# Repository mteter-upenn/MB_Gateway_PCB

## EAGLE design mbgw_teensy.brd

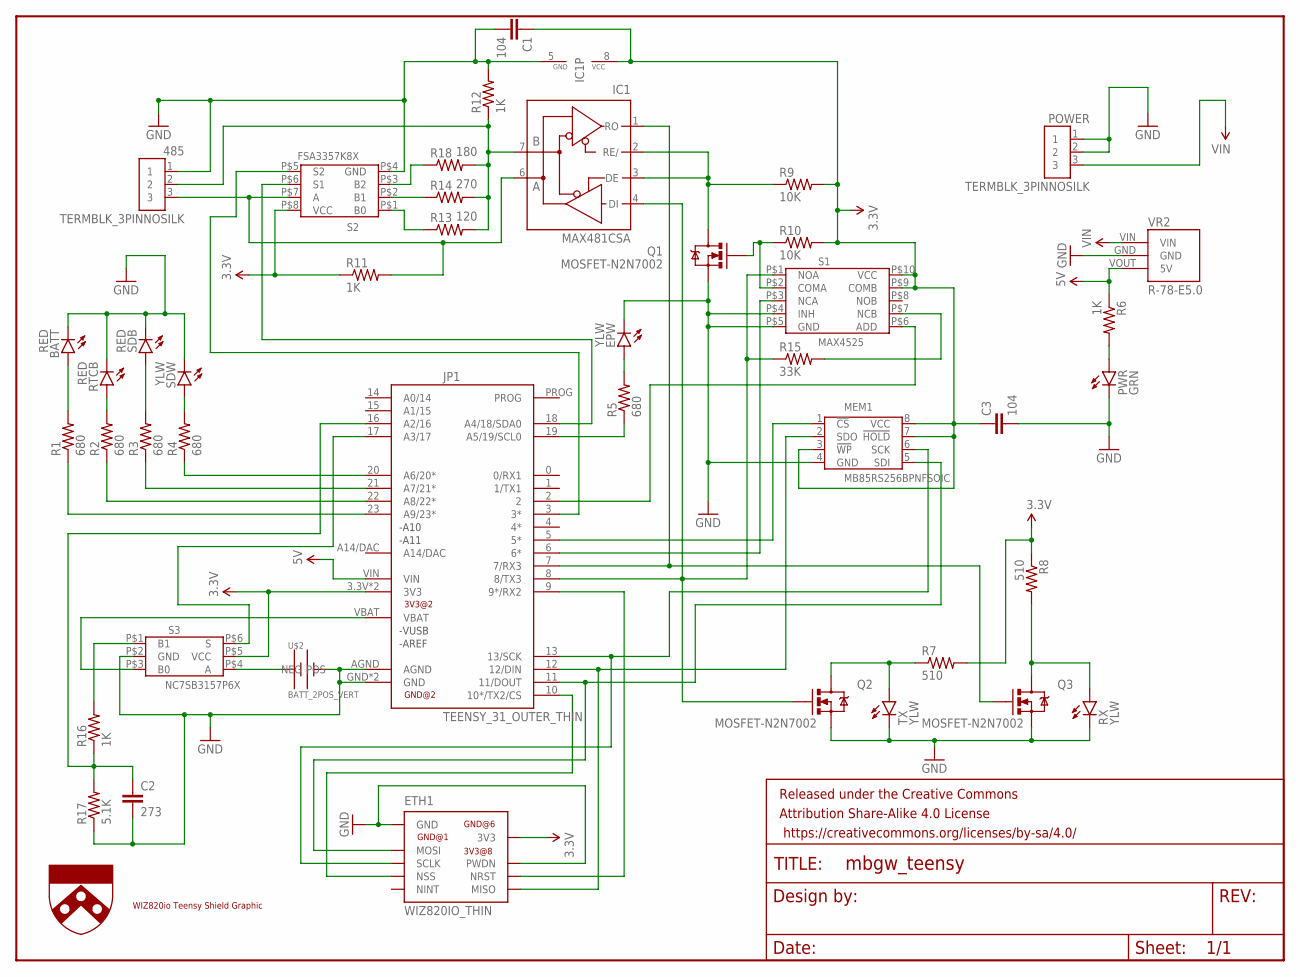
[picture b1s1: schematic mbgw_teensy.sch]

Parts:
485: TERMBLK_3PINNOSILK; TERMBLK_3PIN_90_NOSILK
BATT: RED; LED-0603
C1, C3: 104; 0603-CAP
C2: 273; 0603-CAP
EPW: YLW; LED-0603
ETH1: WIZ820IO_THIN
FRAME1: FRAME-LETTERNO_PACKAGE; DUMMY
IC1: MAX481CSA; SO08
JP1: TEENSY_31_OUTER_THIN; TEENSY-3.1_OUTER_THIN
MEM1: MB85RS256BPNFSOIC; SO08
POWER: TERMBLK_3PINNOSILK; TERMBLK_3PIN_90_NOSILK
PWR: GRN; LED-0603
Q1, Q2, Q3: MOSFET-N2N7002; SOT23-3
R1, R2, R3, R4, R5: 680; 0603-RES
R6, R11, R12, R16: 1K; 0603-RES
R7, R8: 510; 0603-RES
R9, R10: 10K; 0603-RES
R13: 120; 0603-RES
R14: 270; 0603-RES
R15: 33K; 0603-RES
R17: 5.1K; 0603-RES
R18: 180; 0603-RES
RTCB: RED; LED-0603
RX: YLW; LED-0603
S1: MAX4525; 3MM_10PIN
S2: FSA3357K8X; 2.3MM_8PIN
S3: NC7SB3157P6X; 1.25MM_6PIN
SDB: RED; LED-0603
SDW: YLW; LED-0603
TX: YLW; LED-0603
U$1: WIZ820_SHLD_OVRLY; WIZ820_SHLD_OVERLAY
U$2: BATT_2POS_VERT; BATTCONN_20MM_VERT
U$4: UPENN_SHIELD_.3_SILK; UPENN_SHIELD_3_SILK
VR2: R-78-E5.0; R-78-EXX

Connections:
3.3V: C1.1, C3.1, ETH1.3V3@7 (3V3), ETH1.3V3@8 (3V3), IC1.8 (VCC), JP1.3.3V (3V3), JP1.3V (3V3), MEM1.3 (!WP!), MEM1.7 (!HOLD!), MEM1.8 (VCC), R7.2, R8.1, R9.2, R10.2, R11.1, S1.P$9 (COMB), S1.P$10 (VCC), S2.P$8 (VCC), S3.P$5 (VCC)
5V: JP1.VIN, R6.1, VR2.VOUT (5V)
GND: 485.1, BATT.C, C1.2, C2.2, C3.2, EPW.C, ETH1.GND@0 (GND), ETH1.GND@1 (GND), ETH1.GND@6 (GND), ETH1.PWDN, IC1.5 (GND), JP1.AGND, JP1.GND, JP1.GND1 (GND), MEM1.4 (GND), POWER.1, POWER.2, PWR.C, Q1.2 (S), Q2.2 (S), Q3.2 (S), R12.2, R17.1, RTCB.C, RX.C, S1.P$4 (INH), S1.P$5 (GND), S2.P$4 (GND), S3.P$2 (GND), SDB.C, SDW.C, TX.C, U$2.NEG, VR2.GND
unnamed: R15.2, S1.P$7 (NCB)
unnamed: JP1.6 (6*), S1.P$3 (NCA)
unnamed: S3.P$4 (A), U$2.POS@1 (POS), U$2.POS@2 (POS)
unnamed: JP1.19 (A5/19/SCL0), R5.1
unnamed: ETH1.NSS, JP1.10 (10*/TX2/CS)
unnamed: ETH1.MOSI, JP1.11 (11/DOUT), MEM1.5 (SDI)
unnamed: ETH1.MISO, JP1.12 (12/DIN), MEM1.2 (SDO)
unnamed: ETH1.SCLK, JP1.13 (13/SCK), MEM1.6 (SCK)
unnamed: JP1.23 (A9/23*), R1.1
unnamed: ETH1.NRST, JP1.9 (9*/RX2)
unnamed: EPW.A, R5.2
unnamed: R13.1, S2.P$1 (B0)
unnamed: 485.2, IC1.7 (B), R12.1, R13.2, R14.2, R18.2
unnamed: PWR.A, R6.2
unnamed: JP1.18 (A4/18/SDA0), S2.P$6 (S1)
unnamed: IC1.1 (RO), JP1.7 (7/RX3), Q3.1 (G)
unnamed: IC1.4 (DI), JP1.8 (8/TX3), Q2.1 (G), R15.1, S1.P$1 (NOA)
unnamed: BATT.A, R1.2
unnamed: R3.2, SDB.A
unnamed: R2.2, RTCB.A
unnamed: R4.2, SDW.A
unnamed: JP1.22 (A8/22*), R2.1
unnamed: JP1.21 (A7/21*), R3.1
unnamed: JP1.20 (A6/20*), R4.1
unnamed: 485.3, IC1.6 (A), R11.2, S2.P$7 (A)
unnamed: Q1.1 (G), R10.1, S1.P$2 (COMA)
unnamed: IC1.2 (RE/), IC1.3 (DE), Q1.3 (D), R9.1
unnamed: Q3.3 (D), R8.2, RX.A
unnamed: Q2.3 (D), R7.1, TX.A
unnamed: R14.1, S2.P$2 (B1)
unnamed: JP1.3 (3*), S2.P$5 (S2)
unnamed: JP1.2, S1.P$6 (ADD)
unnamed: JP1.VBAT, S3.P$3 (B0)
unnamed: R18.1, S2.P$3 (B2)
unnamed: C2.1, JP1.16 (A2/16), R16.1, R17.2
unnamed: JP1.5 (5*), MEM1.1 (!CS!)
unnamed: R16.2, S3.P$1 (B1)
unnamed: JP1.17 (A3/17), S3.P$6 (S)
VIN: POWER.3, VR2.VIN

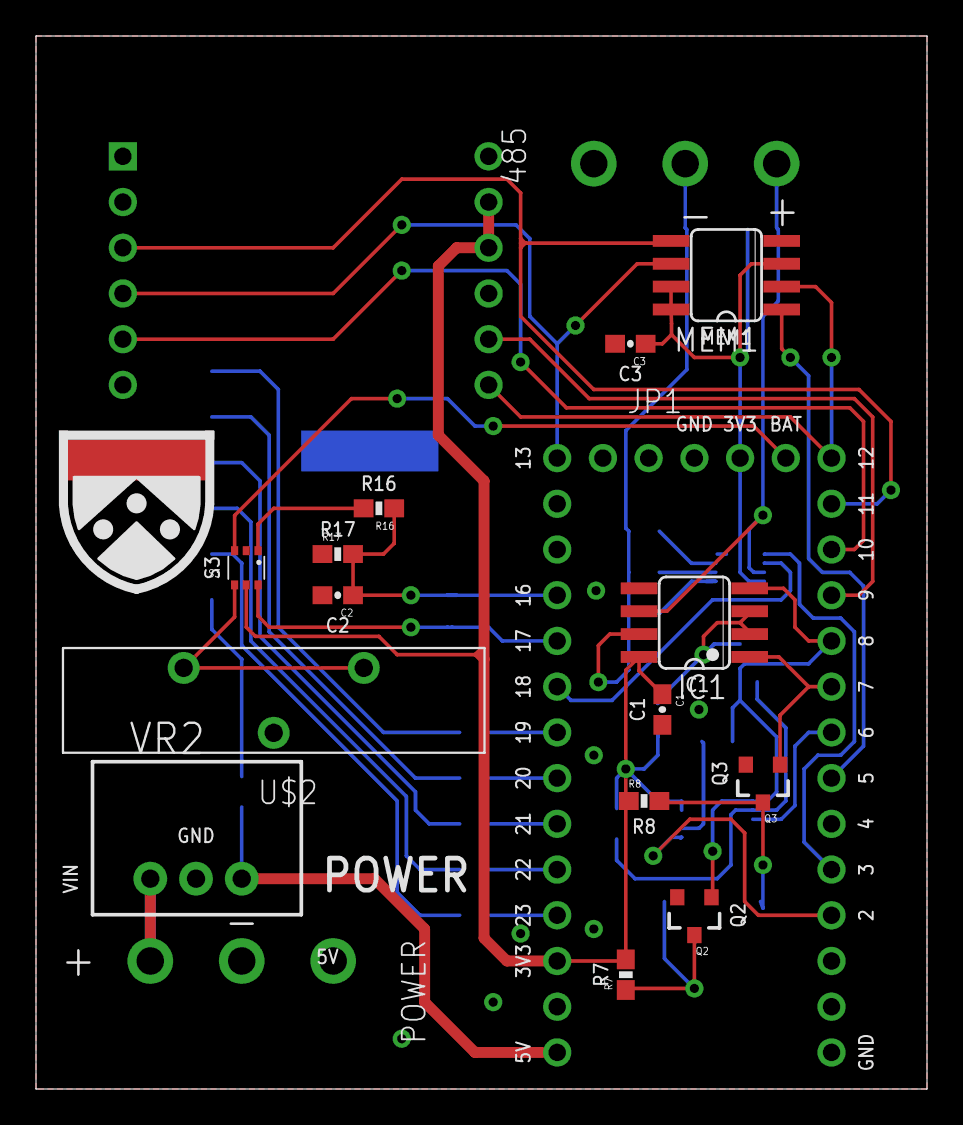
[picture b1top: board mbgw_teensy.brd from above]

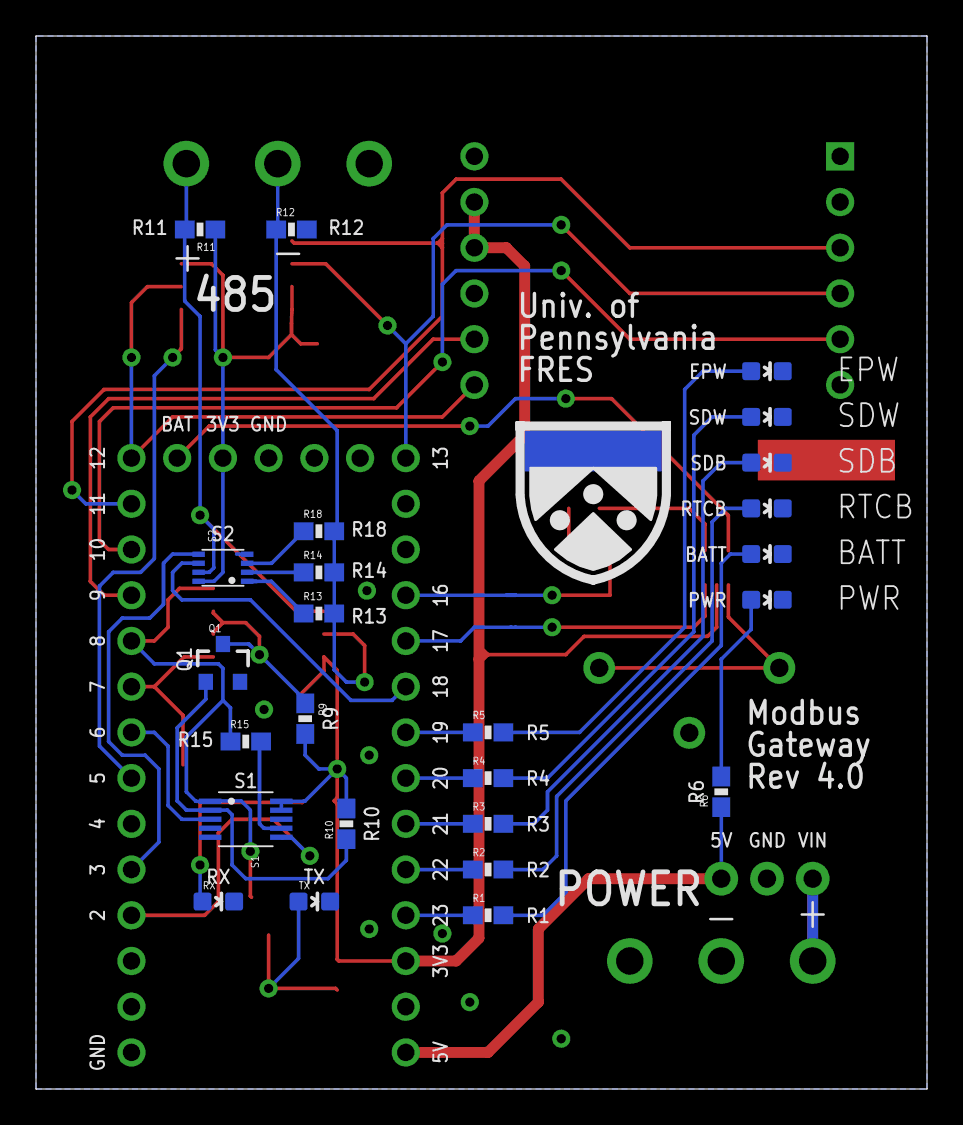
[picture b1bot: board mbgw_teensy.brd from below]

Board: 2 copper layers, 49.5 x 58.5 mm, 47 parts (26 on the bottom side), 42 nets.

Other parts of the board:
U$3: UPENN_SHIELD_.3_SILK; UPENN_SHIELD_3_SILK

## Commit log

2017-03-16 3/16/17, first commit
2017-03-16 3/16/17, board with software switches for term resistor and tx/p6 control
2017-03-20 3/20/17, continue adjusting for stretched board
2017-03-21 3/21/17, all chips connected, make sure everything visible
2017-03-22 3/22/17, gerber files made
2017-03-23 3/23/17, added BOM
2017-03-23 3/23/17, fram instead of eeprom memory
2017-03-23 3/23/17, refreshed gerbers

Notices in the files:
parts and their libraries:
SparkFun-Aesthetics: Licensing: Creative Commons ShareAlike 4.0 International - https://creativecommons.org/licenses/by-sa/4.0
SparkFun-Aesthetics: Released under the Creative Commons Attribution Share-Alike 4.0 License
SparkFun-Aesthetics: https://creativecommons.org/licenses/by-sa/4.0
